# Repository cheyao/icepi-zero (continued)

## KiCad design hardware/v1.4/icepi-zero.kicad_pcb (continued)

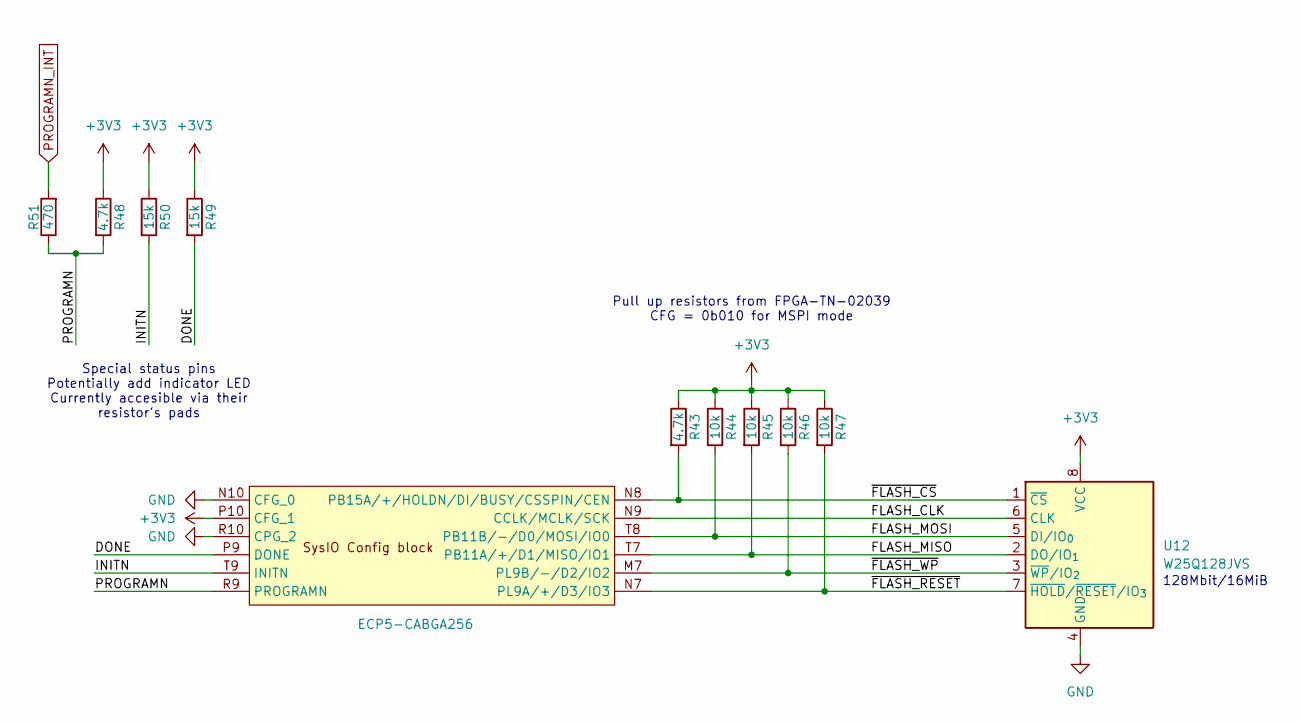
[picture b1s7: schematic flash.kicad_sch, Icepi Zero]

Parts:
R43: 4.7k; R_0402_1005Metric; Manufactuer Part Number 0402WGF4701TCE; LCSC Part # C25900
R44, R45, R46, R47: 10k; R_0402_1005Metric; Manufactuer Part Number 0402WGF1002TCE; LCSC Part # C25744
R48: 4.7k; R_0402_1005Metric; Manufactuer Part Number 0402WGF4701TCE; LCSC Part # C25756
R49, R50: 15k; R_0402_1005Metric; Manufactuer Part Number 0402WGF1502TCE; LCSC Part # C25756
R51: 470; R_0402_1005Metric; Manufactuer Part Number 0402WGF4700TCE; LCSC Part # C25117
U1: ECP5-CABGA256; BGA-256_14.0x14.0mm_Layout16x16_P0.8mm_Ball0.45mm_Pad0.32mm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; Manufactuer Part Number LFE5U-25F-6BG256C; LCSC Part # C1521614
U12: W25Q128JVS; SOIC-8_5.3x5.3mm_P1.27mm; Manufactuer Part Number W25Q128JVSIQ; LCSC Part # C97521

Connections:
+3V3: R43.1, R44.1, R45.1, R46.1, R47.1, R48.1, R49.1, R50.1, U1.P10 (CFG_1), U12.8 (VCC); also elsewhere on the board
/Flash/DONE: R49.2, U1.P9 (DONE)
/Flash/FLASH_CLK: U1.N9 (CCLK/MCLK/SCK), U12.6 (CLK)
/Flash/FLASH_MISO: R45.2, U1.T7 (PB11A/+/D1/MISO/IO1), U12.2 (DO/IO_{1})
/Flash/FLASH_MOSI: R44.2, U1.T8 (PB11B/-/D0/MOSI/IO0), U12.5 (DI/IO_{0})
/Flash/INITN: R50.2, U1.T9 (INITN)
/Flash/PROGRAMN: R48.2, R51.1, U1.R9 (PROGRAMN)
/Flash/~FLASH_CS: R43.2, U1.N8 (PB15A/+/HOLDN/DI/BUSY/CSSPIN/CEN), U12.1 (~CS)
/Flash/~FLASH_RESET: R47.2, U1.N7 (PL9A/+/D3/IO3), U12.7 (~HOLD/~RESET/IO_{3})
/Flash/~FLASH_WP: R46.2, U1.M7 (PL9B/-/D2/IO2), U12.3 (~WP/IO_{2})
GND: U1.N10 (CFG_0), U1.R10 (CPG_2), U12.4 (GND); also elsewhere on the board
PROGRAMN_INT: R51.2; also elsewhere on the board

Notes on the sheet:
128Mbit/16MiB
Special status pins Potentially add indicator LED Currently accesible via their resistor's pads
Pull up resistors from FPGA-TN-02039 CFG = 0b010 for MSPI mode

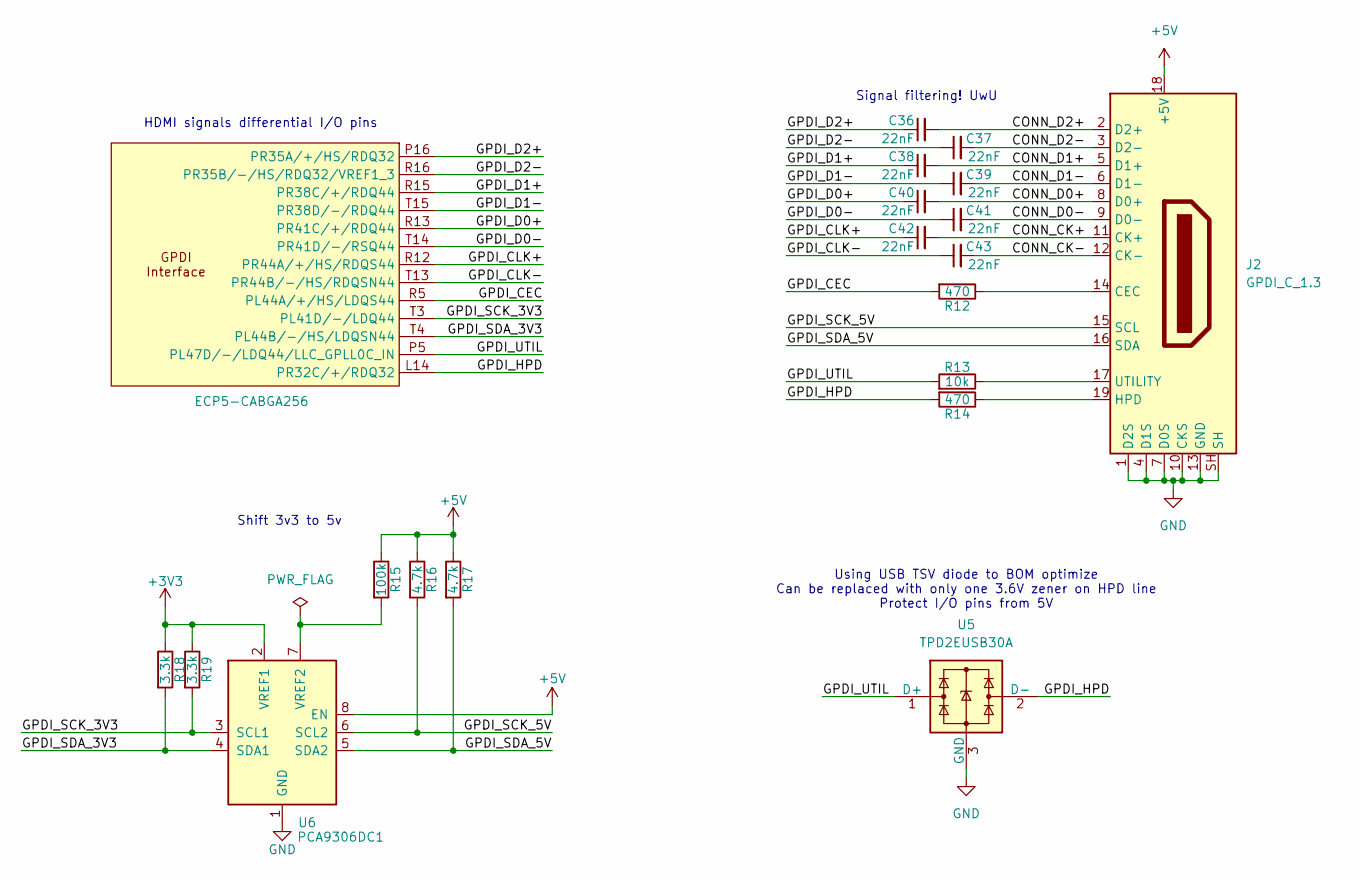
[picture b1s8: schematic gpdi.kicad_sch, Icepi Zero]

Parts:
C36, C37, C38, C39, C40, C41, C42, C43: 22nF; C_0402_1005Metric; Manufactuer Part Number 0402B223K500NT; LCSC Part # C1532
J2: GPDI_C_1.3; XKB Connection A71-05H4-111N1; Manufactuer Part Number A71-05H4-111N1; LCSC Part # C2682170
R12, R14: 470; R_0402_1005Metric; Manufactuer Part Number 0402WGF4700TCE; LCSC Part # C25117
R13: 10k; R_0402_1005Metric; Manufactuer Part Number 0402WGF1002TCE; LCSC Part # C25744
R15: 100k; R_0402_1005Metric; Manufactuer Part Number 0402WGF1003TCE; LCSC Part # C25741
R16, R17: 4.7k; R_0402_1005Metric; Manufactuer Part Number 0402WGF4701TCE; LCSC Part # C25900
R18, R19: 3.3k; R_0402_1005Metric; Manufactuer Part Number 0402WGF3301TCE; LCSC Part # C25890
U1: ECP5-CABGA256; BGA-256_14.0x14.0mm_Layout16x16_P0.8mm_Ball0.45mm_Pad0.32mm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; Manufactuer Part Number LFE5U-25F-6BG256C; LCSC Part # C1521614
U5: TPD2EUSB30A; Texas_DRT-3; Manufactuer Part Number TPD2EUSB30ADRTR; LCSC Part # C3011197
U6: PCA9306DC1; VSSOP-8_2.3x2mm_P0.5mm; Manufactuer Part Number PCA9306DC1; LCSC Part # C129510

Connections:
+3V3: R18.1, R19.1, U6.2 (VREF1); also elsewhere on the board
+5V: J2.18 (+5V), R15.1, R16.1, R17.1, U6.8 (EN); also elsewhere on the board
/GPDI/CONN_CK+: C42.2, J2.11 (CK+)
/GPDI/CONN_CK-: C43.2, J2.12 (CK-)
/GPDI/CONN_D0+: C40.2, J2.8 (D0+)
/GPDI/CONN_D0-: C41.2, J2.9 (D0-)
/GPDI/CONN_D1+: C38.2, J2.5 (D1+)
/GPDI/CONN_D1-: C39.2, J2.6 (D1-)
/GPDI/CONN_D2+: C36.2, J2.2 (D2+)
/GPDI/CONN_D2-: C37.2, J2.3 (D2-)
/GPDI/GPDI_CEC: R12.2, U1.R5 (PL44A/+/HS/LDQS44)
/GPDI/GPDI_CLK+: C42.1, U1.R12 (PR44A/+/HS/RDQS44)
/GPDI/GPDI_CLK-: C43.1, U1.T13 (PR44B/-/HS/RDQSN44)
/GPDI/GPDI_D0+: C40.1, U1.R13 (PR41C/+/RDQ44)
/GPDI/GPDI_D0-: C41.1, U1.T14 (PR41D/-/RSQ44)
/GPDI/GPDI_D1+: C38.1, U1.R15 (PR38C/+/RDQ44)
/GPDI/GPDI_D1-: C39.1, U1.T15 (PR38D/-/RDQ44)
/GPDI/GPDI_D2+: C36.1, U1.P16 (PR35A/+/HS/RDQ32)
/GPDI/GPDI_D2-: C37.1, U1.R16 (PR35B/-/HS/RDQ32/VREF1_3)
/GPDI/GPDI_HPD: R14.2, U1.L14 (PR32C/+/RDQ32), U5.2 (D-)
/GPDI/GPDI_SCK_3V3: R19.2, U1.T3 (PL41D/-/LDQ44), U6.3 (SCL1)
/GPDI/GPDI_SCK_5V: J2.15 (SCL), R16.2, U6.6 (SCL2)
/GPDI/GPDI_SDA_3V3: R18.2, U1.T4 (PL44B/-/HS/LDQSN44), U6.4 (SDA1)
/GPDI/GPDI_SDA_5V: J2.16 (SDA), R17.2, U6.5 (SDA2)
/GPDI/GPDI_UTIL: R13.2, U1.P5 (PL47D/-/LDQ44/LLC_GPLL0C_IN), U5.1 (D+)
GND: J2.1 (D2S), J2.4 (D1S), J2.7 (D0S), J2.10 (CKS), J2.13 (GND), J2.SH, U5.3 (GND), U6.1 (GND); also elsewhere on the board
unnamed: J2.14 (CEC), R12.1
unnamed: J2.19 (HPD), R14.1
unnamed: J2.17 (UTILITY), R13.1
unnamed: R15.2, U6.7 (VREF2)

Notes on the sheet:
Shift 3v3 to 5v
Using USB TSV diode to BOM optimize Can be replaced with only one 3.6V zener on HPD line Protect I/O pins from 5V
HDMI signals differential I/O pins
Signal filtering! UwU

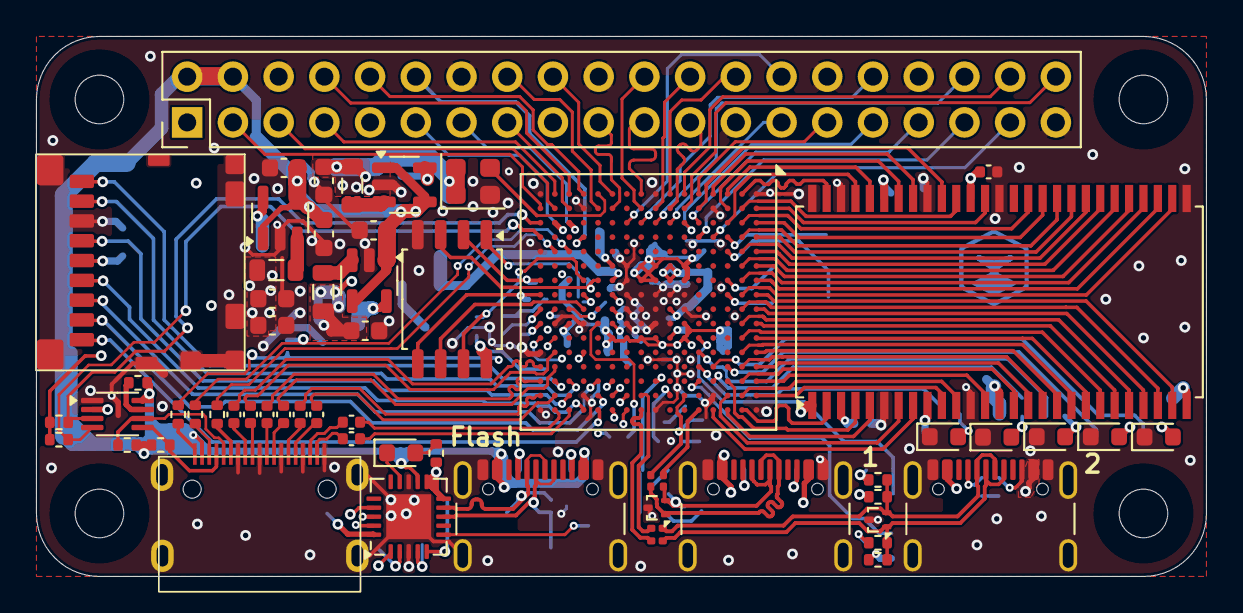
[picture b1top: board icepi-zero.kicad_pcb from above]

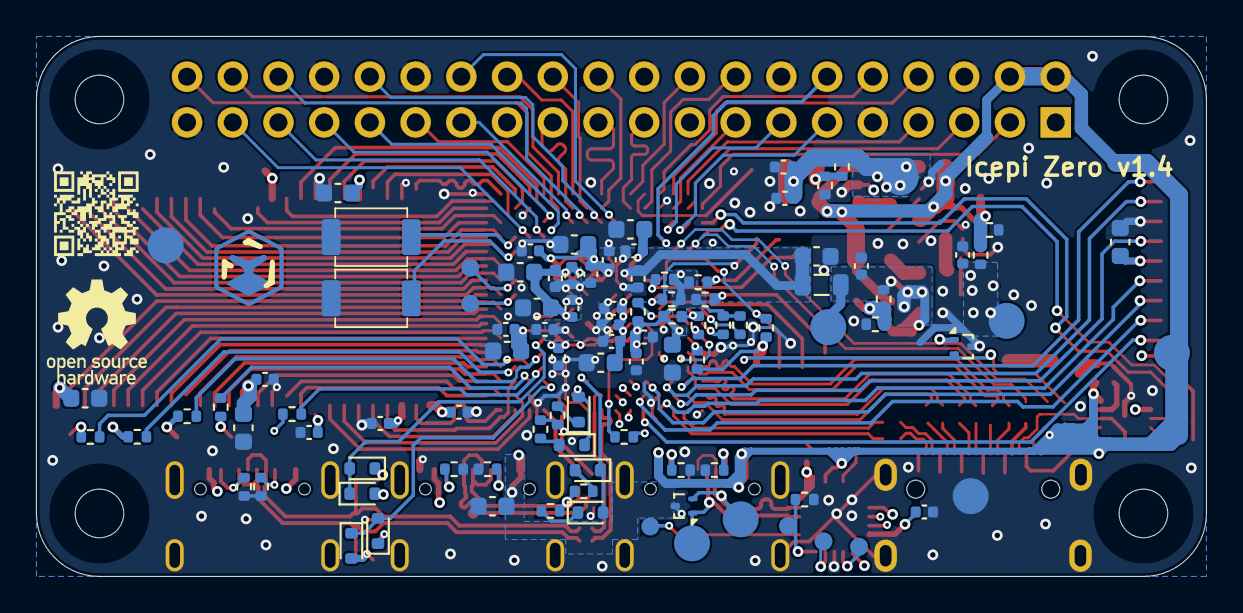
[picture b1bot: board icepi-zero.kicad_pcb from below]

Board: 4 copper layers, 65.0 x 30.0 mm, 163 parts (100 on the bottom side), 177 nets.

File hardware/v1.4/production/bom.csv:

Designator,Footprint,Quantity,Value,LCSC Part #
"C1, C10, C14, C16, C17, C20, C24, C25, C26, C27, C28, C29, C31, C32, C35, C44, C46, C47, C48, C49, C5, C50, C6, C7, C8, C9",0402,26,100nF,C307331
"C11, C12, C13, C18, C19, C33, C45",0603,7,22uF,C59461
"C15, C2, C21, C22, C23, C3, C30, C34, C4, C51, C52, C53, C54",0603,13,10uF,C19702
"C36, C37, C38, C39, C40, C41, C42, C43",0402,8,22nF,C1532
"D1, D2, D3, D4, D5",0603,5,WHITE,C2290
"D10, D11, D12, D13, D6, D7, D8, D9",D_SOD-523,8,1N914WT,C2836064
D14,0603,1,RED,C2286
FB1,0805,1,100R@100MHz,C74480
J2,XKB Connection A71-05H4-111N1,1,GPDI_C_1.3,C2682170
"J3, J4, J5",USB_C_Receptacle_GCT_USB4105-xx-A_16P_TopMnt_Horizontal,3,USB_C_Receptacle_USB2.0_14P,C2765186
J6,microSD_HC_SOFNG_TF-008,1,Micro_SD_Card_Det2,C428465
"L1, L2, L3",0805,3,2.2uH,C107322
"R1, R2, R20, R21, R3, R32, R33, R4, R42, R5",0402,10,1.1k,C140223
"R10, R22, R23, R34, R35, R49, R50, R8",0402,8,15k,C25756
"R11, R18, R19",0402,3,3.3k,C25890
"R12, R14, R51",0402,3,470,C25117
"R13, R44, R45, R46, R47, R6",0402,6,10k,C25744
R15,0402,1,100k,C25741
"R16, R17, R38, R39, R40, R41, R43, R9",0402,8,4.7k,C25900
"R24, R25, R26, R29, R36, R37",0402,6,5.1k,C25905
"R27, R28, R30, R31",0201,4,27,C473051
R48,0402,1,4.7k,C25756
R7,0402,1,12k,C25752
"SW1, SW2",switch_button_TS-1088-AR02016,2,SW_Push,C720477
U1,BGA-256_14.0x14.0mm_Layout16x16_P0.8mm_Ball0.45mm_Pad0.32mm_NSMD,1,ECP5-CABGA256,C1521614
"U10, U5, U7, U8",Texas_DRT-3,4,TPD2EUSB30A,C3011197
U11,TSOP-II-54_22.2x10.16mm_P0.8mm,1,W9825G6KH,C62246
U12,SOIC-8_5.3x5.3mm_P1.27mm,1,W25Q128JVS,C97521
"U2, U3, U4",SOT-23-5,3,TLV62569DBV,C141836
U6,VSSOP-8_2.3x2mm_P0.5mm,1,PCA9306DC1,C129510
U9,QFN-20-1EP_4x4mm_P0.5mm_EP2.5x2.5mm,1,FT231XQ,C132159
Y1,Oscillator_SMD_SiT_PQFN-4Pin_2.5x2.0mm,1,SG-8018CG 50.000000MHz,C390526

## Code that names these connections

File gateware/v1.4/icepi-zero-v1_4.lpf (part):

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IOBUF  PORT "gpdi_dn[3]" IO_TYPE=LVCMOS33D DRIVE=4;

LOCATE COMP "gpdi_cec" SITE "R5";
IOBUF  PORT "gpdi_cec" IO_TYPE=LVCMOS33 PULLMODE=NONE PULLMODE=UP DRIVE=4;
LOCATE COMP "gpdi_sck" SITE "T3";
IOBUF  PORT "gpdi_sck" IO_TYPE=LVCMOS33 PULLMODE=UP DRIVE=4;
LOCATE COMP "gpdi_sda" SITE "T4";
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IOBUF  PORT "sd_csn" IO_TYPE=LVCMOS33 PULLMODE=UP DRIVE=4;

LOCATE COMP "sd_clk" SITE "P15";
IOBUF  PORT "sd_clk" IO_TYPE=LVCMOS33 PULLMODE=UP DRIVE=4;
LOCATE COMP "sd_cmd" SITE "N16";
IOBUF  PORT "sd_cmd" IO_TYPE=LVCMOS33 PULLMODE=UP DRIVE=4;
LOCATE COMP "sd_det" SITE "M16";
IOBUF  PORT "sd_det" IO_TYPE=LVCMOS33 PULLMODE=UP DRIVE=4;

# USB
LOCATE COMP "usb_dp[0]" SITE "F15";
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LOCATE COMP "flash_csn" SITE "N8";
IOBUF  PORT "flash_csn" IO_TYPE=LVCMOS33 PULLMODE=UP DRIVE=4;
LOCATE COMP "flash_clk" SITE "N9";
IOBUF  PORT "flash_clk" IO_TYPE=LVCMOS33 PULLMODE=UP DRIVE=4;
LOCATE COMP "flash_mosi" SITE "T8";
IOBUF  PORT "flash_mosi" IO_TYPE=LVCMOS33 PULLMODE=UP DRIVE=4;
LOCATE COMP "flash_miso" SITE "T7";
IOBUF  PORT "flash_miso" IO_TYPE=LVCMOS33 PULLMODE=UP DRIVE=4;
LOCATE COMP "flash_wpn" SITE "M7";
IOBUF  PORT "flash_wpn" IO_TYPE=LVCMOS33 PULLMODE=UP DRIVE=4;
LOCATE COMP "flash_resetn" SITE "N7";
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
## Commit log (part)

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2025-05-30 add name of the license of the firmware
2025-05-30 typo
2025-05-30 add note about bitstream retention
2026-01-04 Initial commit for hardware v2.0
2026-01-04 Added 54-TFPGA chip, front routing
2026-01-04 Front routing for memory chip
2026-01-04 Front memory routs done
2026-01-04 Remaining memory routs
2026-01-04 Remaining memory data lines done
2026-01-04 Power lines
2026-01-04 Almost done power lines
2026-01-04 Power lines done
2026-01-04 Minor fix
2026-01-04 Authoring
2026-01-04 Added 3d models for buttons
2026-01-10 Update user buttons to 2
